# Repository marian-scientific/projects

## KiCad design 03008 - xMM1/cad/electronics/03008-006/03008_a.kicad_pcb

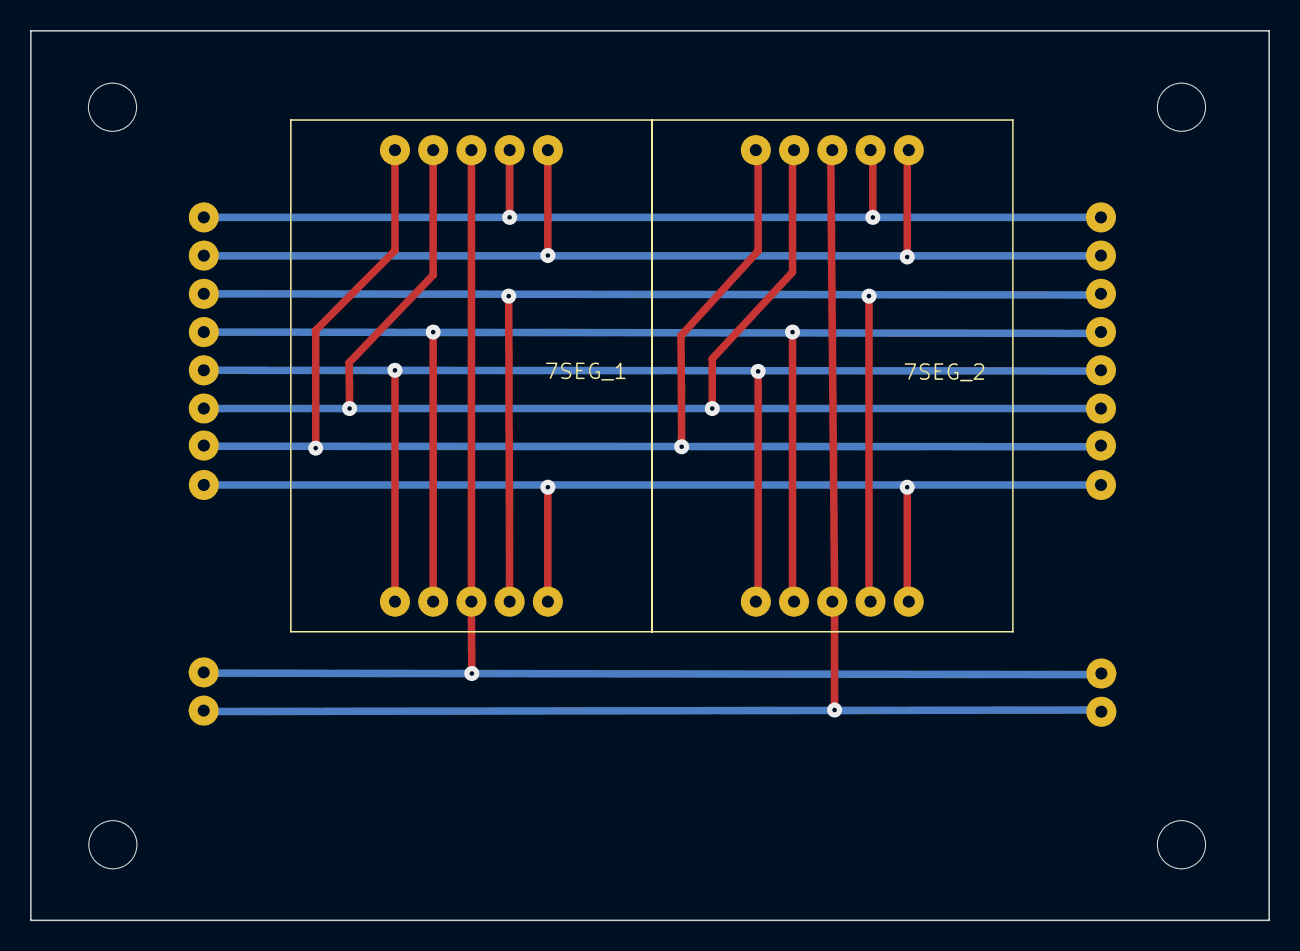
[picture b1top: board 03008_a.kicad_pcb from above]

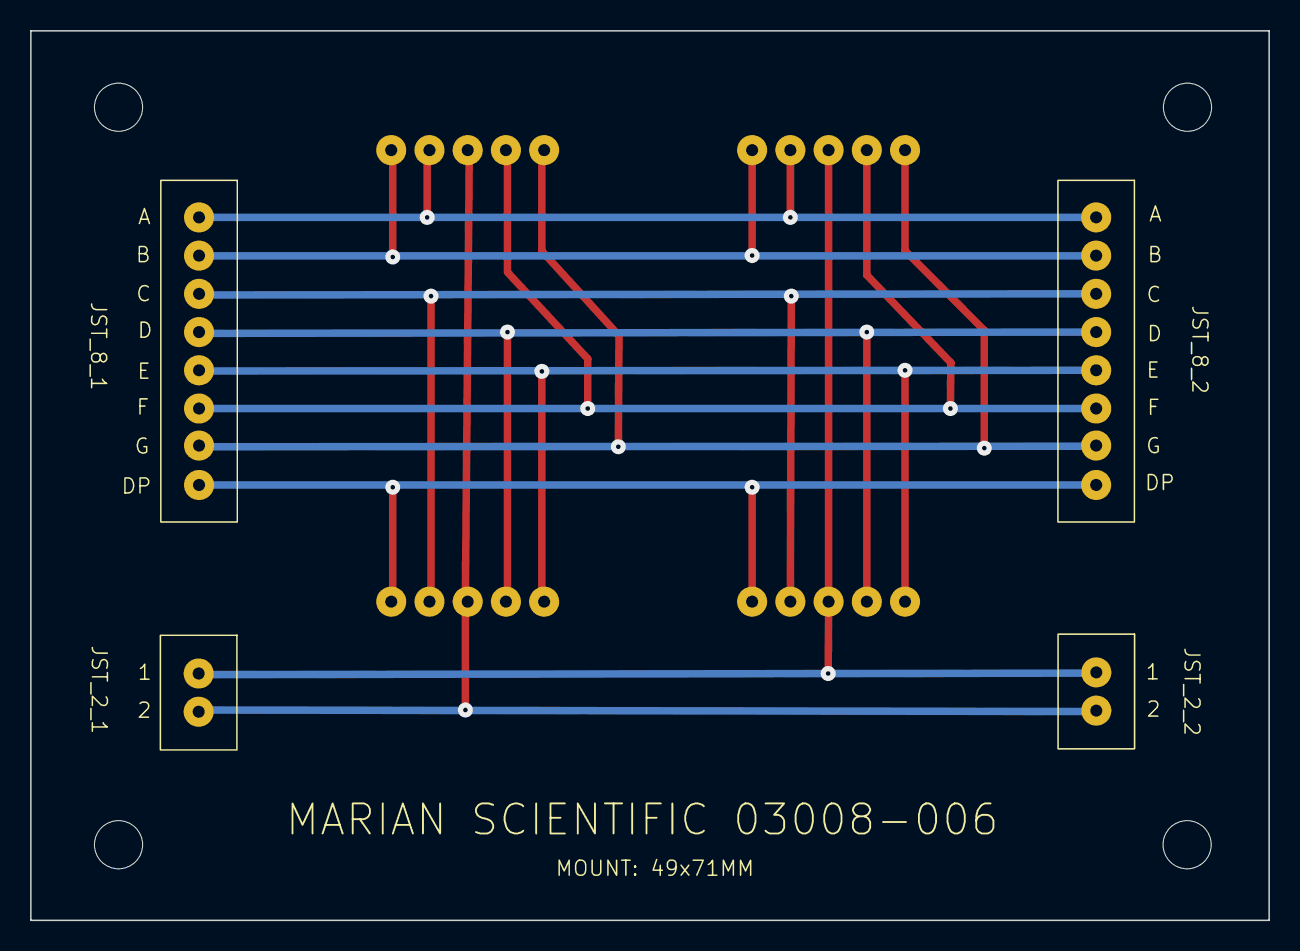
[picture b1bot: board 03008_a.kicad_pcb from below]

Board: 2 copper layers, 82.3 x 59.1 mm, 6 parts (4 on the bottom side), 10 nets, no tracks yet.

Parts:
7SEG_1, 7SEG_2: 7SEGMENT_34x24
JST_2_1, JST_2_2: JST_2
JST_8_1, JST_8_2: JST_8

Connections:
unnamed: 7SEG_1.4 (A), 7SEG_2.4 (A), JST_8_1.1, JST_8_2.1
unnamed: 7SEG_1.5 (B), 7SEG_2.5 (B), JST_8_1.2, JST_8_2.2
unnamed: 7SEG_1.9 (C), 7SEG_2.9 (C), JST_8_1.3, JST_8_2.3
unnamed: 7SEG_1.3 (COMMON), 7SEG_1.8 (COMMON), JST_2_1.1, JST_2_2.1
unnamed: 7SEG_1.7 (D), 7SEG_2.7 (D), JST_8_1.4, JST_8_2.4
unnamed: 7SEG_1.10 (DP), 7SEG_2.10 (DP), JST_8_1.8, JST_8_2.8
unnamed: 7SEG_1.6 (E), 7SEG_2.6 (E), JST_8_1.5, JST_8_2.5
unnamed: 7SEG_1.2 (F), 7SEG_2.2 (F), JST_8_1.6, JST_8_2.6
unnamed: 7SEG_1.1 (G), 7SEG_2.1 (G), JST_8_1.7, JST_8_2.7
unnamed: 7SEG_2.3 (COMMON), 7SEG_2.8 (COMMON), JST_2_1.2, JST_2_2.2

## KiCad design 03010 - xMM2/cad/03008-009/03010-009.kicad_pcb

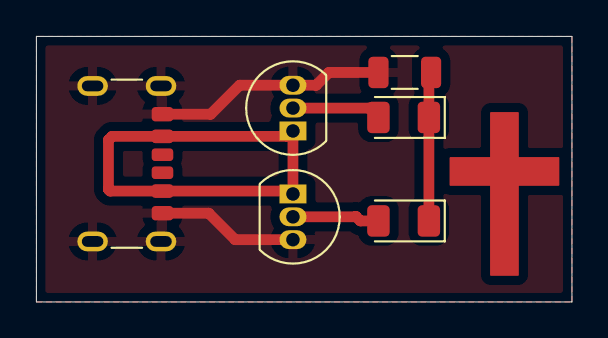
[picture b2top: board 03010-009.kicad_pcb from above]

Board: 2 copper layers, 29.8 x 14.8 mm, 6 parts (0 on the bottom side), 5 nets.

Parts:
D1, D2: LED; LED_1206_3216Metric
J1: USB_C_Receptacle_PowerOnly_6P; USB_C_Receptacle_GCT_USB4125-xx-x_6P_TopMnt_Horizontal
R1: R; R_1206_3216Metric
U1, U2: A1104xLH; TO-92_Inline

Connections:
unnamed: D1.2 (A), U1.2 (V_{OUT})
unnamed: D1.1 (K), D2.1 (K), R1.2
unnamed: D2.2 (A), U2.2 (V_{OUT})
unnamed: J1.A12 (GND), J1.B12 (GND), J1.S1 (SHIELD), R1.1, U1.3 (GND), U2.3 (GND)
unnamed: J1.A9 (VBUS), J1.B9 (VBUS), U1.1 (V_{CC}), U2.1 (V_{CC})

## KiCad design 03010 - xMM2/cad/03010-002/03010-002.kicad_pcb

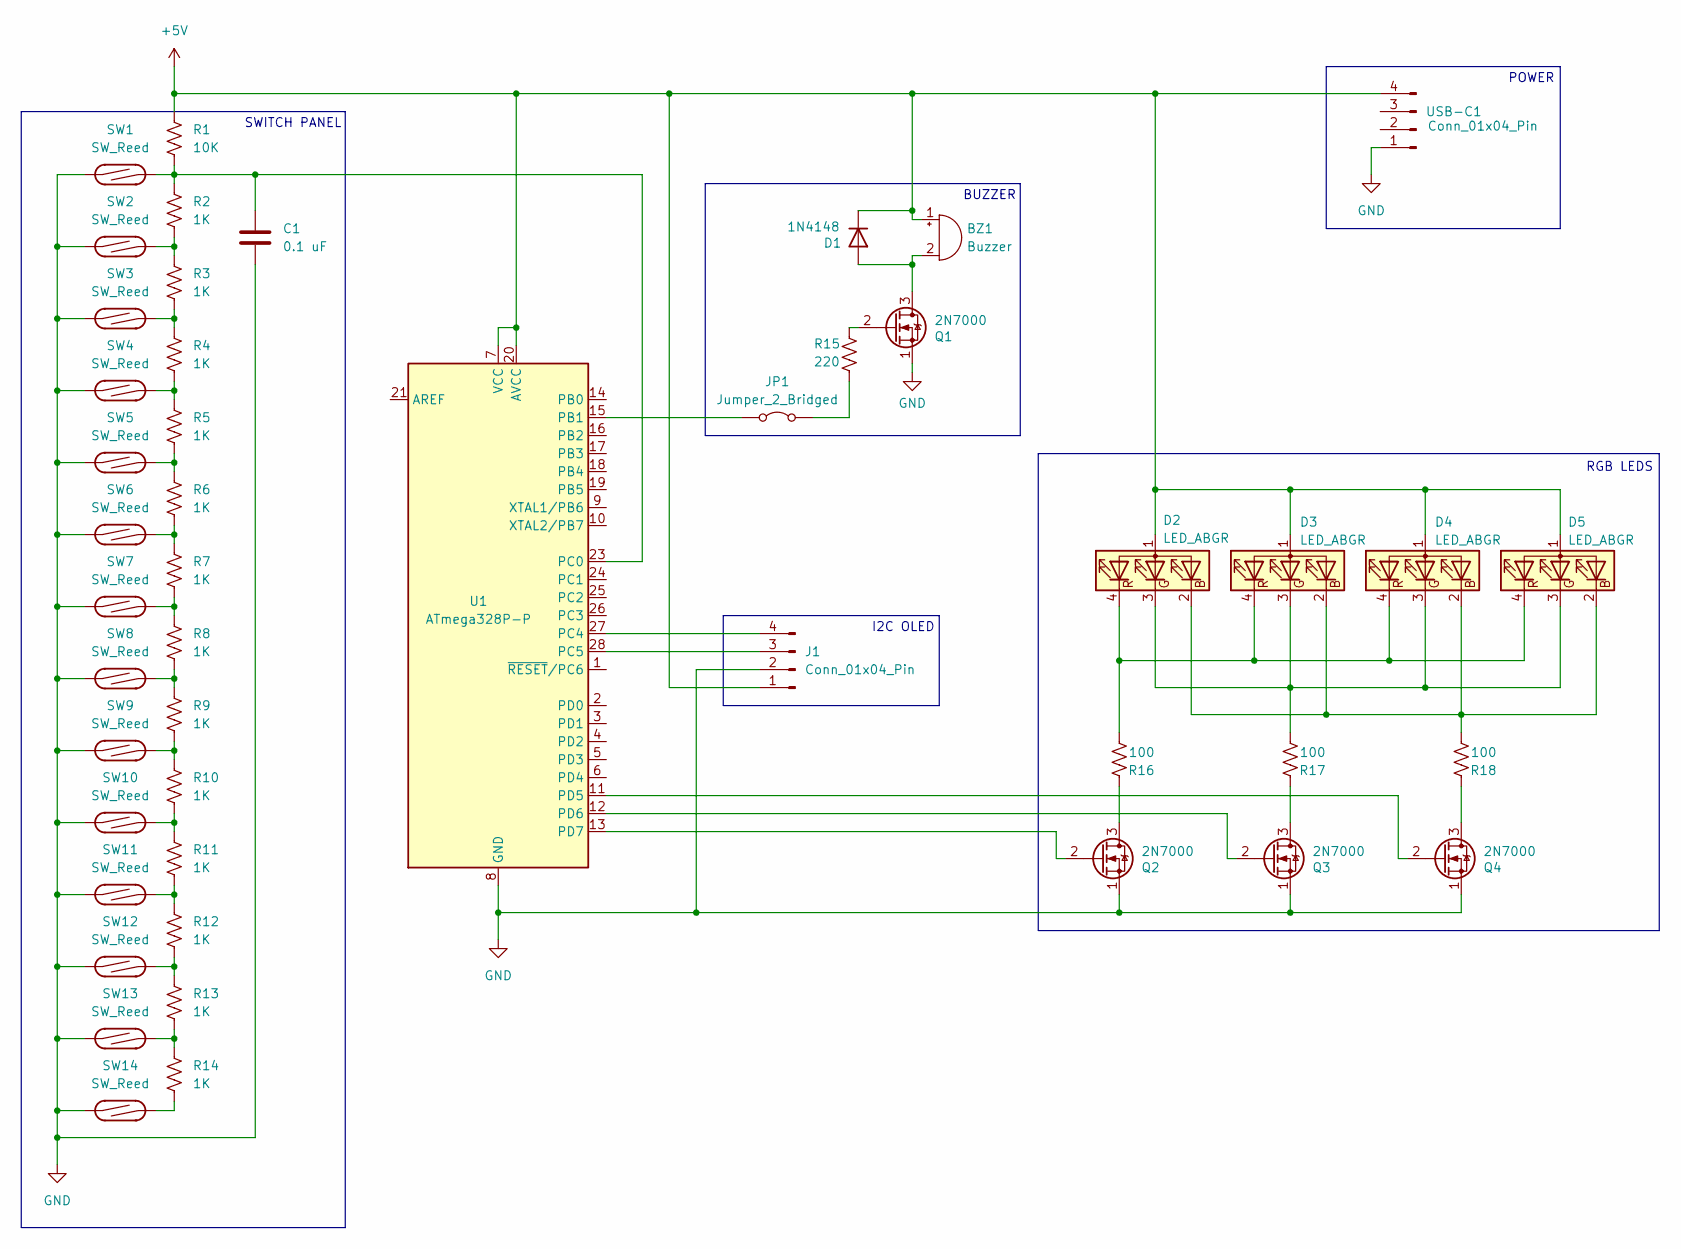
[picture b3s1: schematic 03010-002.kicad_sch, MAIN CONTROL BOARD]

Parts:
BZ1: Buzzer; Buzzer_12x9.5RM7.6
C1: 0.1 uF; C_Disc_D5.1mm_W3.2mm_P5.00mm
D1: 1N4148; D_DO-35_SOD27_P7.62mm_Horizontal
D2, D3, D4, D5: LED_ABGR; LED_D5.0mm-4_RGB
J1: Conn_01x04_Pin; JST_XH_B4B-XH-A_1x04_P2.50mm_Vertical
JP1: Jumper_2_Bridged; PinHeader_1x02_P2.54mm_Vertical
Q1, Q2, Q3, Q4: 2N7000; TO-92_Inline
R1: 10K; R_Axial_DIN0207_L6.3mm_D2.5mm_P10.16mm_Horizontal
R2, R3, R4, R5, R6, R7, R8, R9, R10, R11, R12, R13, R14: 1K; R_Axial_DIN0207_L6.3mm_D2.5mm_P10.16mm_Horizontal
R15: 220; R_Axial_DIN0207_L6.3mm_D2.5mm_P10.16mm_Horizontal
R16, R17, R18: 100; R_Axial_DIN0207_L6.3mm_D2.5mm_P10.16mm_Horizontal
SW1, SW2, SW3, SW4, SW5, SW6, SW7, SW8, SW9, SW10, SW11, SW12, SW13, SW14: SW_Reed; MS_REED_SWITCH
U1: ATmega328P-P; DIP-28_W7.62mm
USB-C1: Conn_01x04_Pin; JST_XH_B4B-XH-A_1x04_P2.50mm_Vertical

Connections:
+5V: BZ1.1 (+), D1.1 (K), D2.1 (A), D3.1 (A), D4.1 (A), D5.1 (A), J1.1, R1.1, U1.7 (VCC), U1.20 (AVCC), USB-C1.4
GND: C1.2, J1.2, Q1.1 (S), Q2.1 (S), Q3.1 (S), Q4.1 (S), SW1.1, SW2.1, SW3.1, SW4.1, SW5.1, SW6.1, SW7.1, SW8.1, SW9.1, SW10.1, SW11.1, SW12.1, SW13.1, SW14.1, U1.8 (GND), U1.22 (GND), USB-C1.1
unnamed: BZ1.2 (-), D1.2 (A), Q1.3 (D)
unnamed: D2.2 (BK), D3.2 (BK), D4.2 (BK), D5.2 (BK), R18.2
unnamed: D2.3 (GK), D3.3 (GK), D4.3 (GK), D5.3 (GK), R17.2
unnamed: D2.4 (RK), D3.4 (RK), D4.4 (RK), D5.4 (RK), R16.2
unnamed: J1.3, U1.28 (PC5)
unnamed: J1.4, U1.27 (PC4)
unnamed: JP1.1 (A), U1.15 (PB1)
unnamed: JP1.2 (B), R15.2
unnamed: Q1.2 (G), R15.1
unnamed: Q2.3 (D), R16.1
unnamed: Q2.2 (G), U1.13 (PD7)
unnamed: Q3.3 (D), R17.1
unnamed: Q3.2 (G), U1.12 (PD6)
unnamed: Q4.3 (D), R18.1
unnamed: Q4.2 (G), U1.11 (PD5)
unnamed: R2.2, R3.1, SW2.2
unnamed: R3.2, R4.1, SW3.2
unnamed: R4.2, R5.1, SW4.2
unnamed: R5.2, R6.1, SW5.2
unnamed: R6.2, R7.1, SW6.2
unnamed: R7.2, R8.1, SW7.2
unnamed: R8.2, R9.1, SW8.2
unnamed: R9.2, R10.1, SW9.2
unnamed: R10.2, R11.1, SW10.2
unnamed: R11.2, R12.1, SW11.2
unnamed: R12.2, R13.1, SW12.2
unnamed: R13.2, R14.1, SW13.2
unnamed: R14.2, SW14.2
unnamed: C1.1, R1.2, R2.1, SW1.2, U1.23 (PC0)

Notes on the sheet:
BUZZER
RGB LEDS
POWER
I2C OLED
SWITCH PANEL

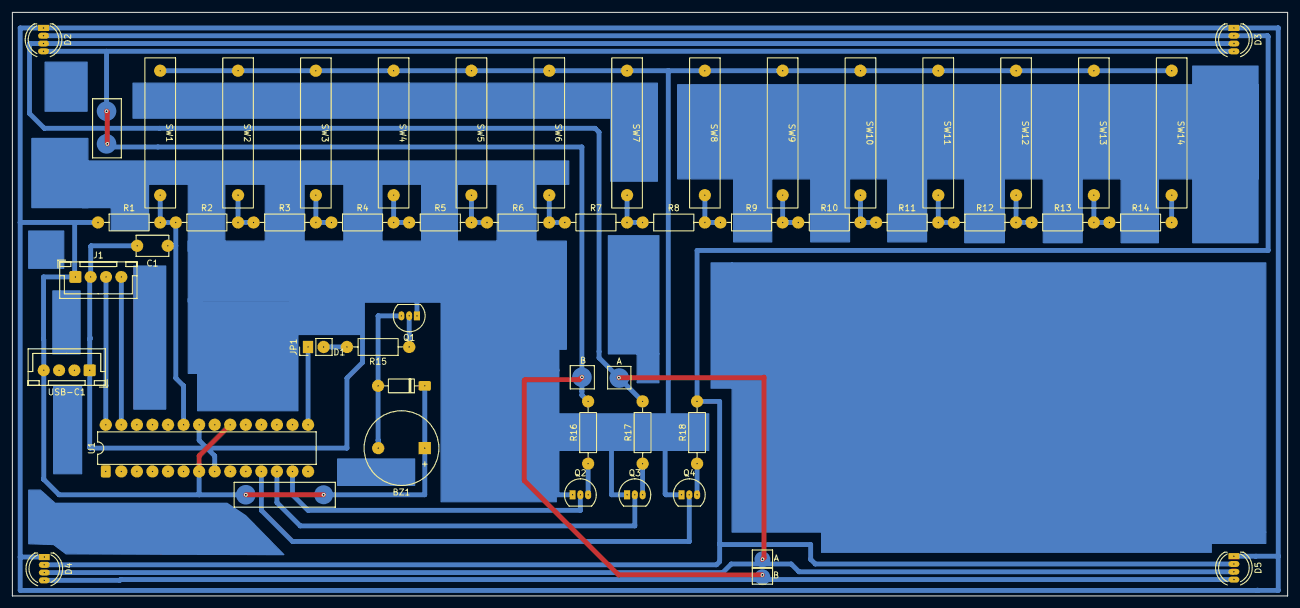
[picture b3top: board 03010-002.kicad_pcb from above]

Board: 2 copper layers, 208.2 x 95.2 mm, 47 parts (0 on the bottom side), 31 nets.

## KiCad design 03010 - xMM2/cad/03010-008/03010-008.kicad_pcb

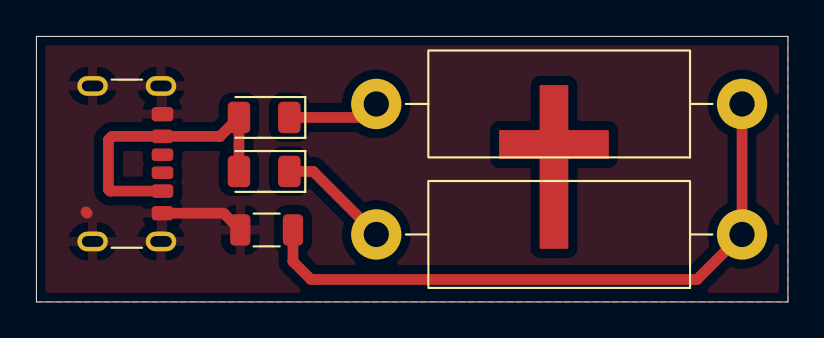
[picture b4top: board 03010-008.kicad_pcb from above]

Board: 2 copper layers, 41.8 x 14.8 mm, 6 parts (0 on the bottom side), 5 nets.

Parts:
D1, D2: LED; LED_1206_3216Metric
J1: USB_C_Receptacle_PowerOnly_6P; USB_C_Receptacle_GCT_USB4125-xx-x_6P_TopMnt_Horizontal
R1: R; R_1206_3216Metric
SW1, SW2: SW_Reed; R_Axial_DIN0614_L14.3mm_D5.7mm_P20.32mm_Horizontal

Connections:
unnamed: D1.2 (A), D2.2 (A), J1.A9 (VBUS), J1.B9 (VBUS)
unnamed: D1.1 (K), SW1.2
unnamed: D2.1 (K), SW2.2
unnamed: J1.A12 (GND), J1.B12 (GND), J1.S1 (SHIELD), R1.2
unnamed: R1.1, SW1.1, SW2.1

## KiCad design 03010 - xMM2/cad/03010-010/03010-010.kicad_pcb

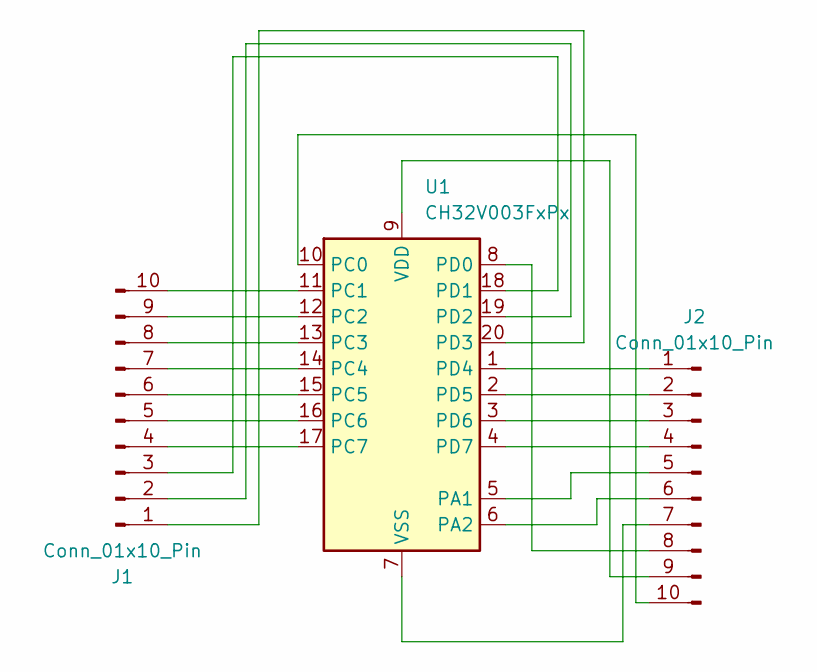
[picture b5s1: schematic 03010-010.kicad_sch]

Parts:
J1, J2: Conn_01x10_Pin; PinHeader_1x10_P2.54mm_Vertical
U1: CH32V003FxPx; TSSOP-20_4.4x6.5mm_P0.65mm

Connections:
unnamed: J1.1, U1.20 (PD3)
unnamed: J1.2, U1.19 (PD2)
unnamed: J1.3, U1.18 (PD1)
unnamed: J1.4, U1.17 (PC7)
unnamed: J1.5, U1.16 (PC6)
unnamed: J1.6, U1.15 (PC5)
unnamed: J1.7, U1.14 (PC4)
unnamed: J1.8, U1.13 (PC3)
unnamed: J1.9, U1.12 (PC2)
unnamed: J1.10, U1.11 (PC1)
unnamed: J2.1, U1.1 (PD4)
unnamed: J2.2, U1.2 (PD5)
unnamed: J2.3, U1.3 (PD6)
unnamed: J2.4, U1.4 (PD7)
unnamed: J2.5, U1.5 (PA1)
unnamed: J2.6, U1.6 (PA2)
unnamed: J2.7, U1.7 (VSS)
unnamed: J2.8, U1.8 (PD0)
unnamed: J2.9, U1.9 (VDD)
unnamed: J2.10, U1.10 (PC0)

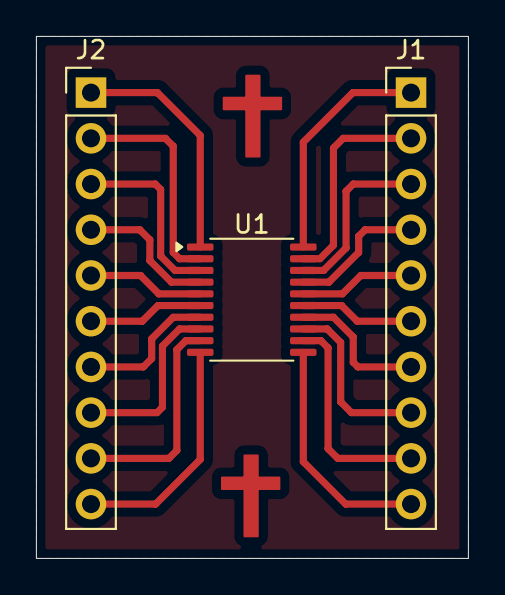
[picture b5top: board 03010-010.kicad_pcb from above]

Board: 2 copper layers, 24.0 x 29.0 mm, 3 parts (0 on the bottom side), 20 nets.

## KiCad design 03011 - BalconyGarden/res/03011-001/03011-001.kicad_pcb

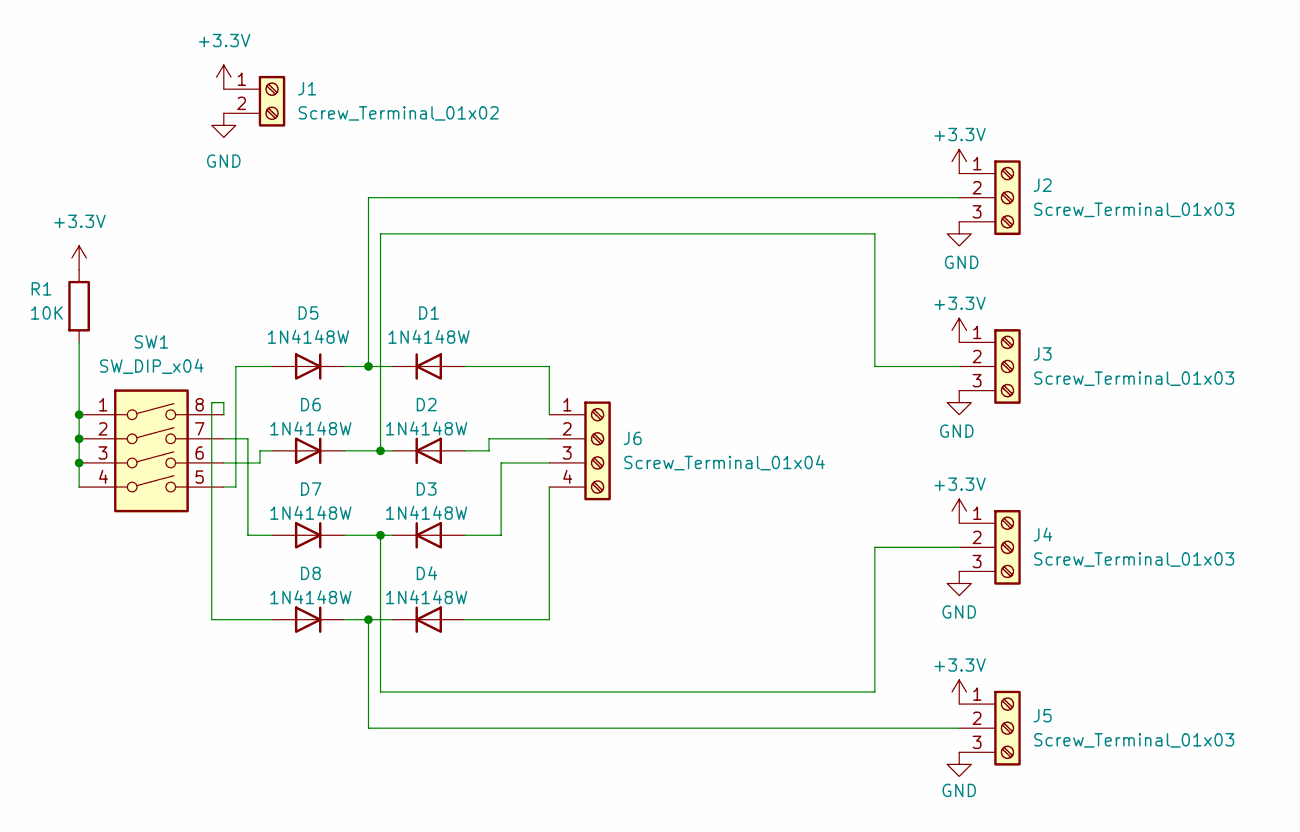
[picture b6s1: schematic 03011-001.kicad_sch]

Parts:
D1, D2, D3, D4, D5, D6, D7, D8: 1N4148W; D_SOD-123
J1: Screw_Terminal_01x02; TerminalBlock_TE_282834-2_1x02_P2.54mm_Horizontal
J2, J3, J4, J5: Screw_Terminal_01x03; TerminalBlock_TE_282834-3_1x03_P2.54mm_Horizontal
J6: Screw_Terminal_01x04; TerminalBlock_Phoenix_MPT-0,5-4-2.54_1x04_P2.54mm_Horizontal
R1: 10K; R_1206_3216Metric
SW1: SW_DIP_x04; SW_DIP_SPSTx04_Slide_9.78x12.34mm_W7.62mm_P2.54mm

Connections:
+3.3V: J1.1, J2.1, J3.1, J4.1, J5.1, R1.1
GND: J1.2, J2.3, J3.3, J4.3, J5.3
unnamed: D1.2 (A), J6.1
unnamed: D1.1 (K), D5.1 (K), J2.2
unnamed: D2.2 (A), J6.2
unnamed: D2.1 (K), D6.1 (K), J3.2
unnamed: D3.2 (A), J6.3
unnamed: D3.1 (K), D7.1 (K), J4.2
unnamed: D4.2 (A), J6.4
unnamed: D4.1 (K), D8.1 (K), J5.2
unnamed: D5.2 (A), SW1.5
unnamed: D6.2 (A), SW1.6
unnamed: D7.2 (A), SW1.7
unnamed: D8.2 (A), SW1.8
unnamed: R1.2, SW1.1, SW1.2, SW1.3, SW1.4

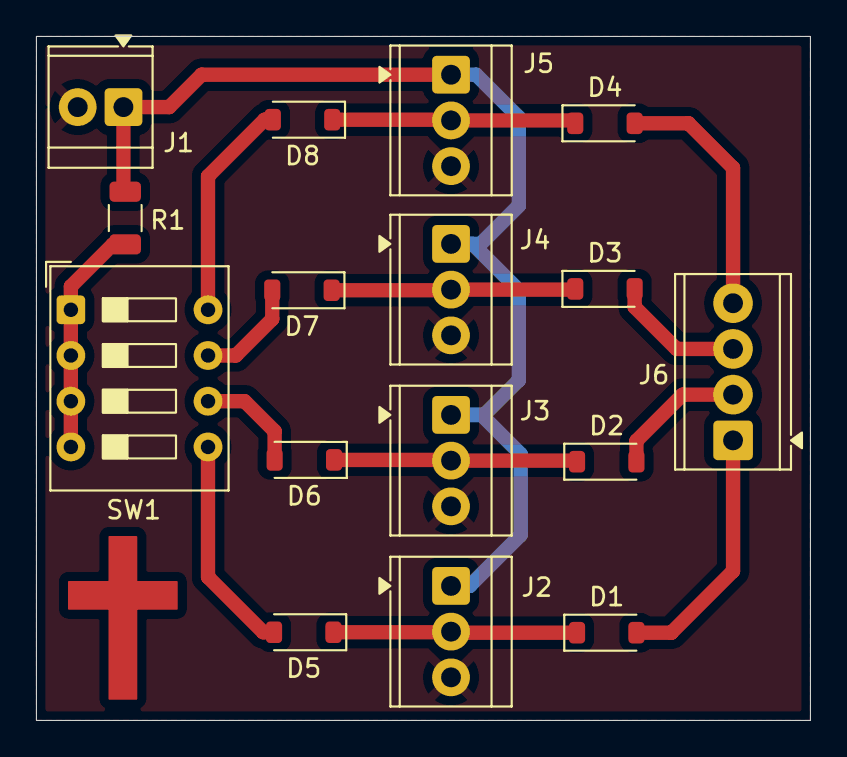
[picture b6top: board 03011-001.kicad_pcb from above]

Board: 2 copper layers, 43.0 x 38.0 mm, 16 parts (0 on the bottom side), 15 nets.

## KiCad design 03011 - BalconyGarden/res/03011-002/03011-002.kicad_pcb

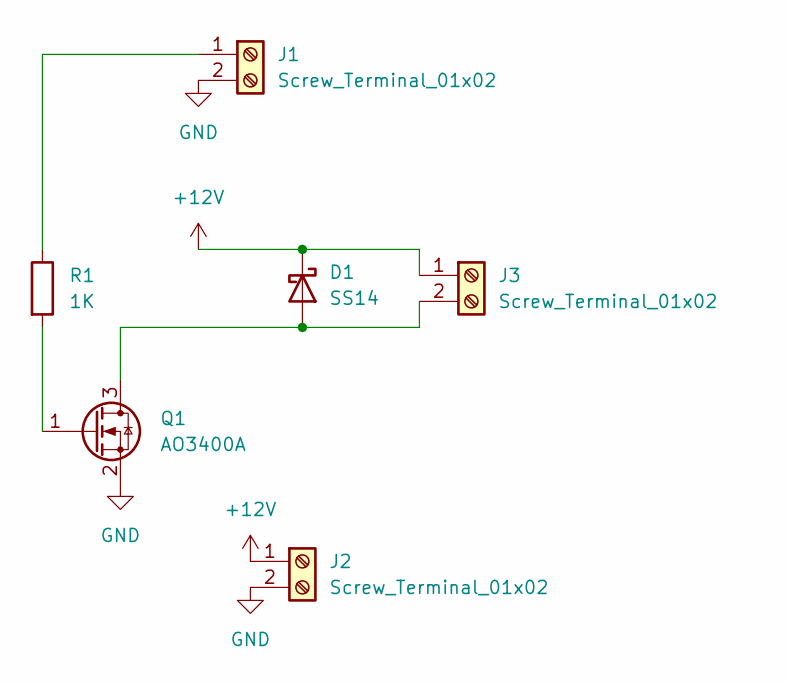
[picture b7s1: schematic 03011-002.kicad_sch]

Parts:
D1: SS14; D_SMA
J1, J2, J3: Screw_Terminal_01x02; TerminalBlock_TE_282834-2_1x02_P2.54mm_Horizontal
Q1: AO3400A; SOT-23
R1: 1K; R_1206_3216Metric

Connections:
+12V: D1.1 (K), J2.1, J3.1
GND: J1.2, J2.2, Q1.2 (S)
unnamed: D1.2 (A), J3.2, Q1.3 (D)
unnamed: J1.1, R1.1
unnamed: Q1.1 (G), R1.2

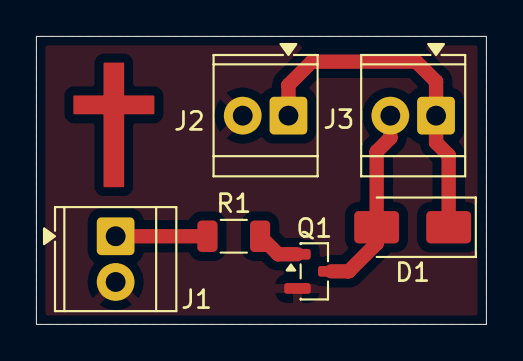
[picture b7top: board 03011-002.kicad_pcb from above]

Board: 2 copper layers, 25.0 x 16.0 mm, 6 parts (0 on the bottom side), 5 nets.
